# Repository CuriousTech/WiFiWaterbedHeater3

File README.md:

# WiFi Waterbed Heater 3 (final)

This is the 3rd and final iteration of this. The GUI is based on my [Universal Remote](https://github.com/CuriousTech/Smart-Universal-Remote) so it has a multi-tile swap gesture interface using the
[WaveShare-ESP32-S3-Touch-LCD-2.8](https://www.waveshare.com/wiki/ESP32-S3-Touch-LCD-2.8).  

The small breakout board is not really needed and uses more space since the only component required is a 4K7 resistor to pull up the DS18B20 signal line, but I already have connectors for everything from the old project. So from left to right: DS18B20, power/slave, LD2410, and AM2320/AM2322 vertically.  The i2c lines have internal pullups.  

The slave board and 3D files from the WB2 project is reposted here as well.  

The web page. Same as previous, but allows drag and drop files over the lower file display areas. The internal files are only used for click and notifications sounds so far. It's just easier than setting up to upload the FFat.  Although SPIFFS or LittleFS can be used instead very easily. The SD card is used for the MP3 player.  

Building: The ino explains the common settings for the IDE like my other projects. I use the Windows Store version because it works best for me. If a library is missing, the error should show a line with a link to where to get it. If not, complain.  
  
A little explanation of the HLK-LD2450 reader: The bottom area of the page represents the detection area. The 5000 (mm) is the X (signed X/2) and Y cutoff. Anything beyond that is zone 2 (outside the room). Zone 2 is also anything painted grey (this sees through walls). This area means lights/fan off. Zome 1 is in the room/lights on and fan off, motion or not. Latch area switches to zone 0/light off and fan on. Hold area is still in bed/zone 0 if latched.

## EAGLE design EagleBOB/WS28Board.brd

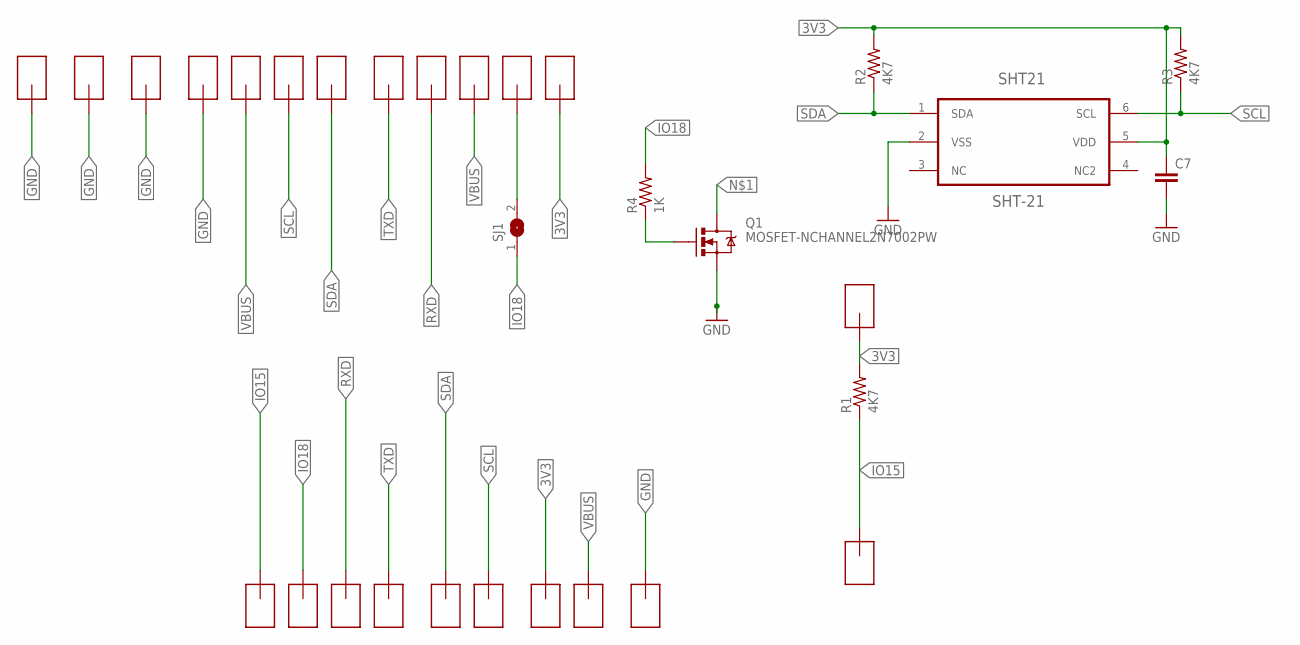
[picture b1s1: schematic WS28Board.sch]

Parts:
C7: CAP0603-CAP; 0603-CAP
GND, GND1, GND2, GND3, GND4: SMD-PAD1
Q1: MOSFET-NCHANNEL2N7002PW; SOT323
R1, R2, R3: 4K7; 0805
R4: 1K; 0805
SHT21: SHT-21; SHT21
SJ1: SJ
U$1, U$2, U$3, U$4, U$5, U$6, U$7, U$8, U$9, U$10, U$11, U$12, U$13, U$14, U$15, U$16, U$17, U$18: SMD-PAD1

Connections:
3V3: C7.1, GND4.>NAME, R1.2, R2.2, R3.2, SHT21.5 (VDD), U$13.>NAME, U$14.>NAME
GND: C7.2, Q1.2 (S), SHT21.2 (VSS), U$1.>NAME, U$10.>NAME, U$15.>NAME, U$16.>NAME, U$17.>NAME
IO15: GND2.>NAME, R1.1, U$18.>NAME
IO18: R4.2, SJ1.1, U$9.>NAME
unnamed: GND.>NAME, Q1.3 (D), SJ1.2
unnamed: Q1.1 (G), R4.1
NC: SHT21.3 (NC)
RXD: U$3.>NAME, U$8.>NAME
SCL: R3.1, SHT21.6 (SCL), U$6.>NAME, U$12.>NAME
SDA: GND1.>NAME, GND3.>NAME, R2.1, SHT21.1 (SDA)
TXD: U$2.>NAME, U$7.>NAME
VBUS: U$4.>NAME, U$5.>NAME, U$11.>NAME

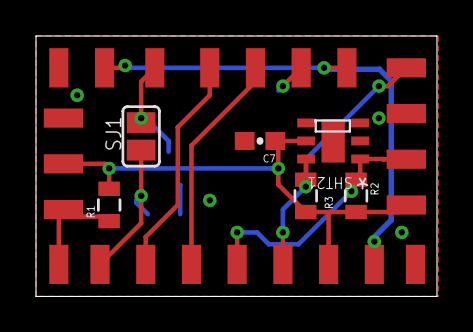
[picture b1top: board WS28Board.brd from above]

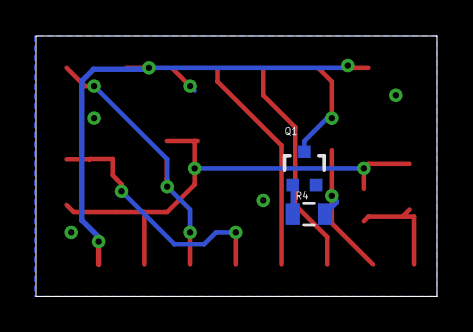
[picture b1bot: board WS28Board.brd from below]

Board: 2 copper layers, 22.3 x 14.5 mm, 31 parts (2 on the bottom side), 11 nets.

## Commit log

2025-02-07 Added async SD read
2025-02-07 async SD read changes
2025-02-07 Added request queue
2025-02-07 Example PC client
2025-02-14 Double row lights tile, fixed notification history
2025-02-14 Full name based switch calls
2025-02-14 bugfix, SD freespace added
2025-02-14 Easier to remove radar here
2025-03-10 Radar optional
2025-03-10 Separated file manager page
2025-03-10 Added parent .. thing
2025-03-10 Support for new fileman
2025-03-10 Better multi-fs file manager
2025-05-07 Added radar zone editor for LD2450
2025-05-07 Added LD2450 reader
2025-05-07 Added edit zone
2025-05-07 Added zone editor
2025-05-07 added array
2025-05-07 Whatever this was
2025-05-10 Added 2 more radar settings
2025-05-10 Added area 2 limiters, 32x32 edit blocks and boundary limit
2025-05-10 Added radar settings
2025-05-17 Correct SD free space
2025-05-17 Extra zone 0 latch thing
2025-05-17 radar zone stuff
2025-05-17 Zone visuals update
2025-05-17 Updated web view
2025-09-07 Changed to esp32 time lib
2025-09-07 Current item highlight
2025-09-07 Changed to esp32 time lib, better wifi reconnect
2025-11-05 Wrong key text in fileman
2026-06-20 1 pixel to the right
2026-06-20 typo
2026-06-20 Refactor uriString class to include pre-allocation
2026-06-20 overly complicated relative paths
2026-06-20 Refactor eeMem to use file system for settings
    Updated file handling for settings storage and improved verification logic.
2026-06-20 Enhance Lights class with timeout and queue updates
    Updated Lights class to include timeout handling and improved queue management.
2026-06-20 Gets temp and rh from HVAC if it's avail
2026-06-20 Removed LD2410 code
2026-06-20 Updated T&H for int version lib
    Updated temperature and humidity measurement logic to use int16_t and adjusted conversion for temperature.
2026-06-20 Changed /iot to just /, better WiFi disconnect handling

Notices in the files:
parts and their libraries:
SparkFun-Resistors: Licensing: Creative Commons ShareAlike 4.0 International - https://creativecommons.org/licenses/by-sa/4.0
SparkFun-Capacitors: Licensing: CC v3.0 Share-Alike You are welcome to use this library for commercial purposes.
